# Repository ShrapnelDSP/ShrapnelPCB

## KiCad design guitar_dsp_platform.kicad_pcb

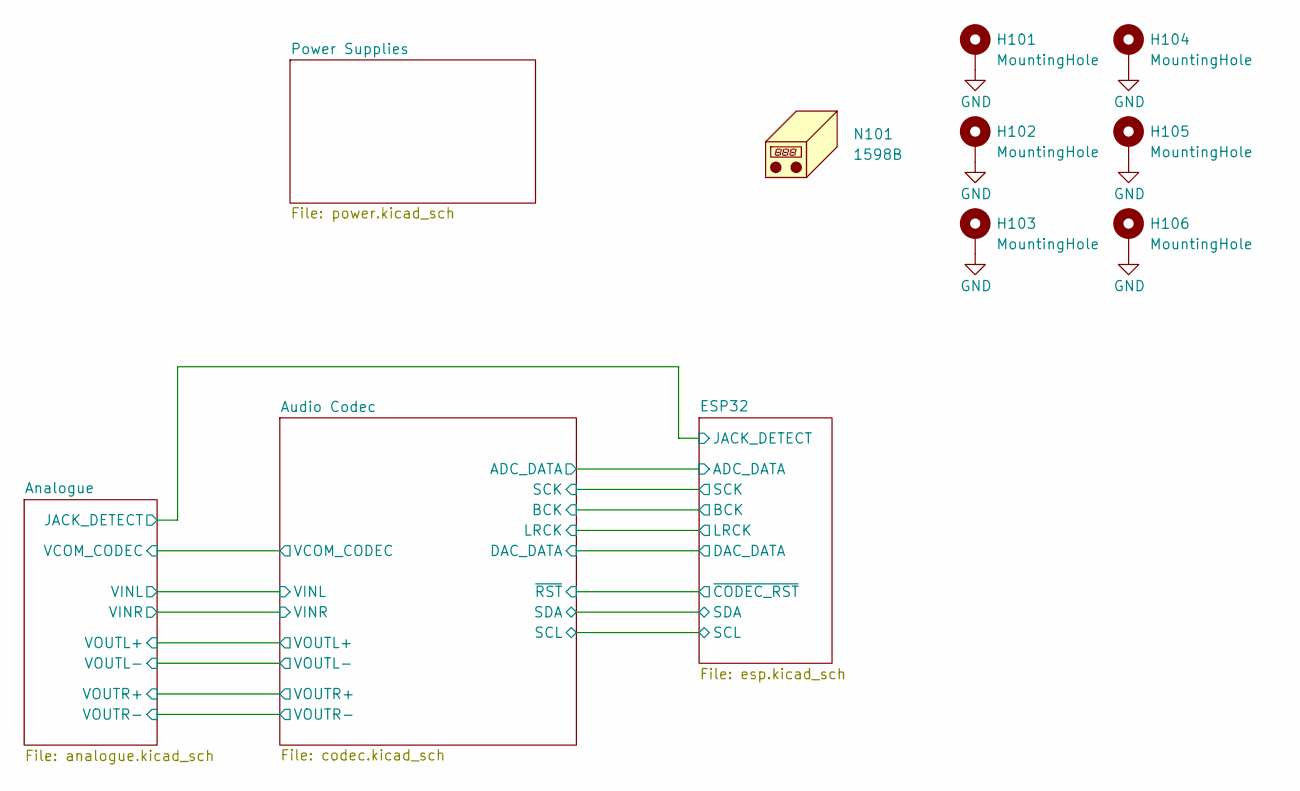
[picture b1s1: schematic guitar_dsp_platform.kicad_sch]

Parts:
H101, H102, H103, H104, H105, H106: MountingHole; 1598B_mounting_hole
N101: 1598B

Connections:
GND: H101.1, H102.1, H103.1, H104.1, H105.1, H106.1; also elsewhere on the board

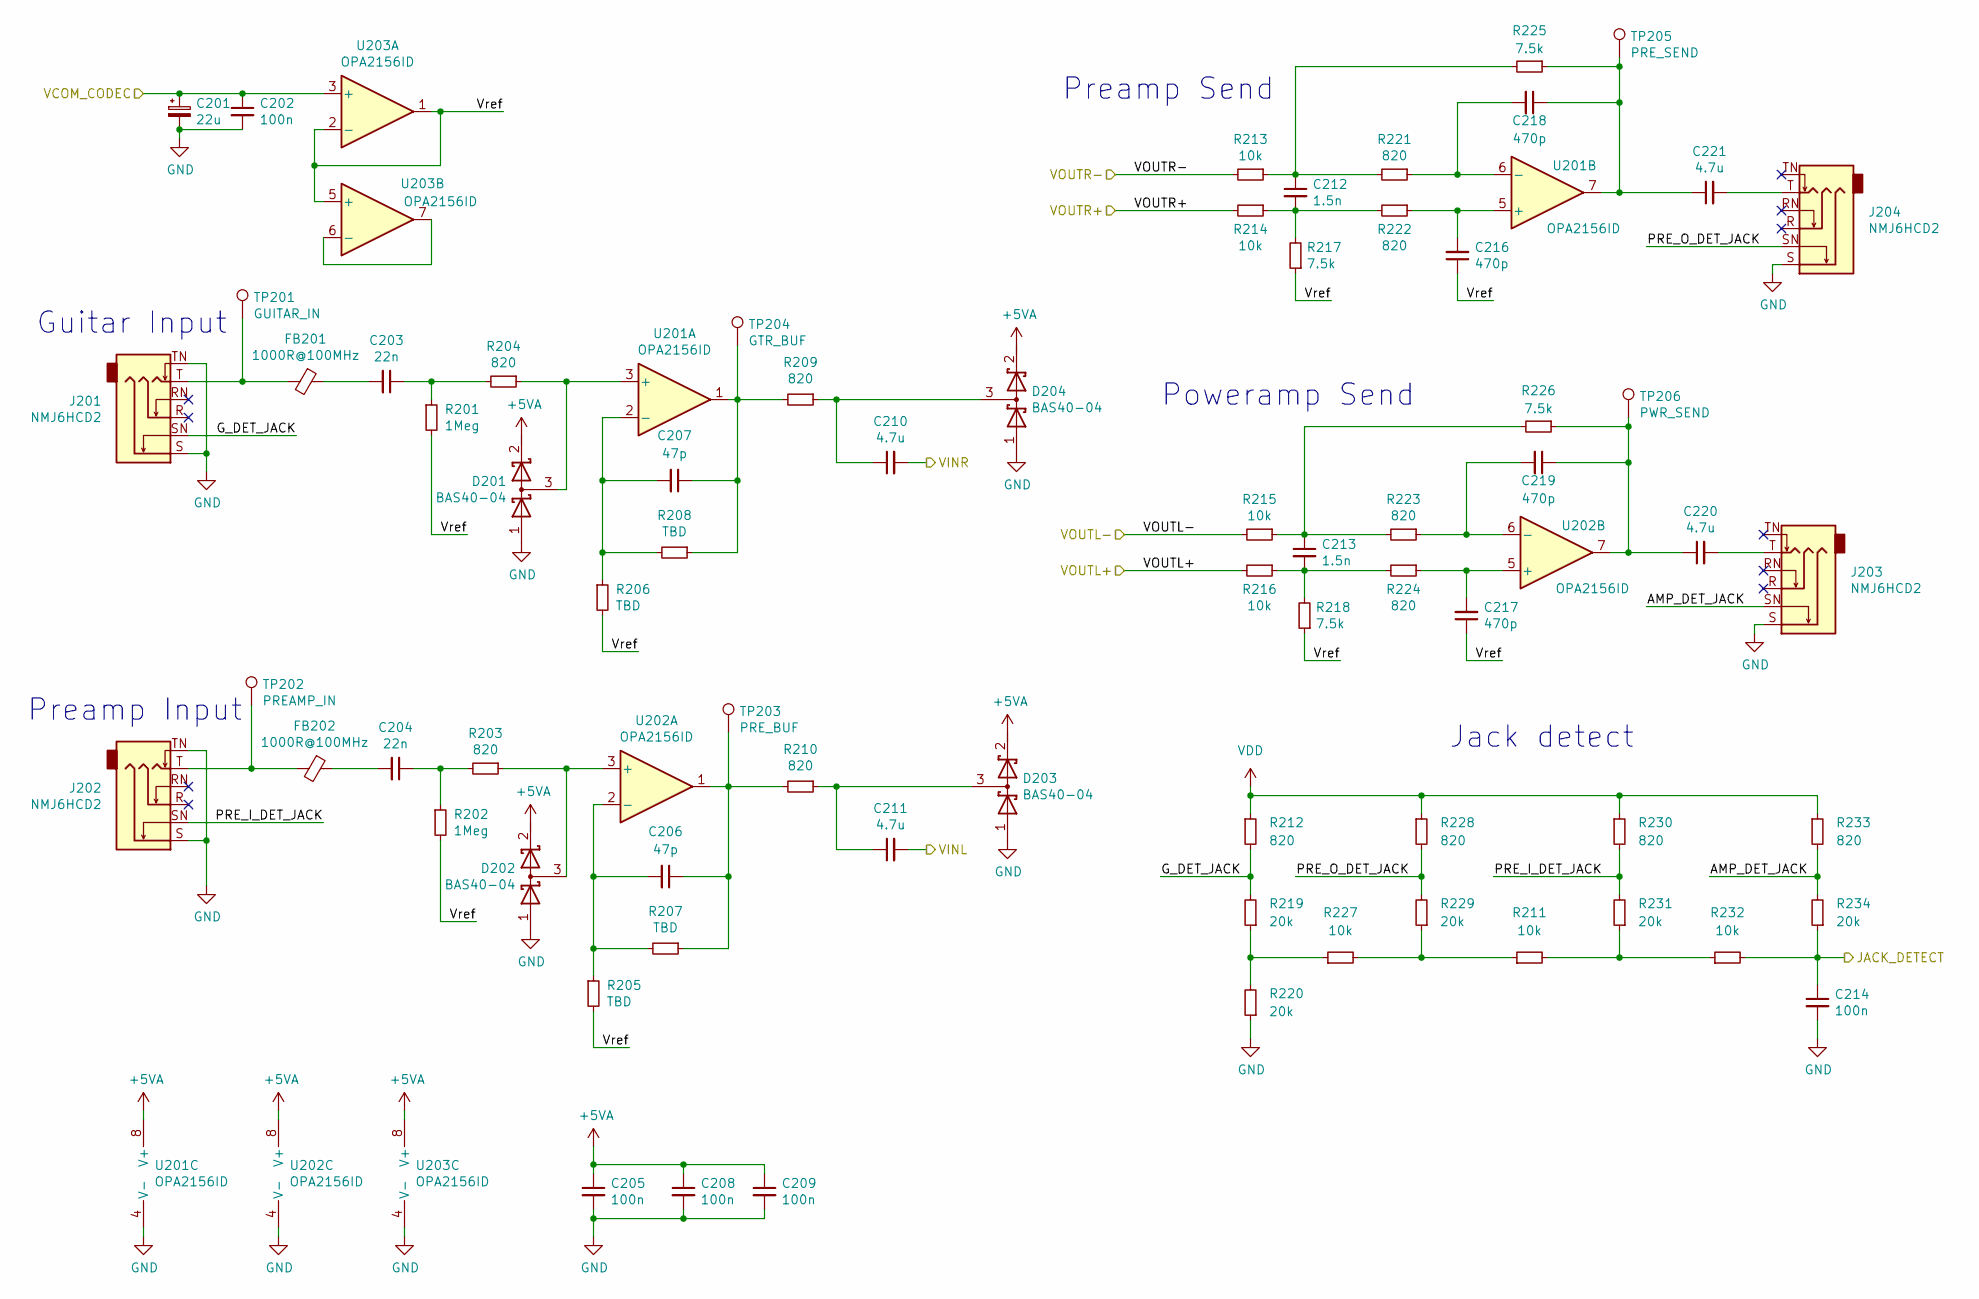
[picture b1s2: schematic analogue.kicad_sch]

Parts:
C201: 22u; CP_Elec_4x5.8
C202, C205, C208, C209, C214: 100n; C_0805_2012Metric_Pad1.18x1.45mm_HandSolder
C203, C204: 22n; C_0805_2012Metric_Pad1.18x1.45mm_HandSolder
C206, C207: 47p; C_0805_2012Metric_Pad1.18x1.45mm_HandSolder
C210, C211, C220, C221: 4.7u; C_Elec_4x5.8
C212, C213: 1.5n; C_0805_2012Metric_Pad1.18x1.45mm_HandSolder
C216, C217, C218, C219: 470p; C_0805_2012Metric_Pad1.18x1.45mm_HandSolder
D201, D202, D203, D204: BAS40-04; SOT-23
FB201, FB202: 1000R@100MHz; R_0805_2012Metric_Pad1.20x1.40mm_HandSolder
J201, J202, J203, J204: NMJ6HCD2; Jack_6.35mm_Neutrik_NMJ6HCD2_Horizontal
R201, R202: 1Meg; R_0805_2012Metric_Pad1.20x1.40mm_HandSolder
R203, R204, R209, R210, R212, R221, R222, R223, R224, R228, R230, R233: 820; R_0805_2012Metric_Pad1.20x1.40mm_HandSolder
R205, R206, R207, R208: TBD; R_0805_2012Metric_Pad1.20x1.40mm_HandSolder
R211, R213, R214, R215, R216, R227, R232: 10k; R_0805_2012Metric_Pad1.20x1.40mm_HandSolder
R217, R218, R225, R226: 7.5k; R_0805_2012Metric_Pad1.20x1.40mm_HandSolder
R219, R220, R229, R231, R234: 20k; R_0805_2012Metric_Pad1.20x1.40mm_HandSolder
TP201: GUITAR_IN; TestPoint_THTPad_D2.0mm_Drill1.0mm
TP202: PREAMP_IN; TestPoint_THTPad_D2.0mm_Drill1.0mm
TP203: PRE_BUF; TestPoint_THTPad_D2.0mm_Drill1.0mm
TP204: GTR_BUF; TestPoint_THTPad_D2.0mm_Drill1.0mm
TP205: PRE_SEND; TestPoint_THTPad_D2.0mm_Drill1.0mm
TP206: PWR_SEND; TestPoint_THTPad_D2.0mm_Drill1.0mm
U201, U202, U203: OPA2156ID; SOIC-8_3.9x4.9mm_P1.27mm

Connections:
+5VA: C205.1, C208.1, C209.1, D201.2 (K), D202.2 (K), D203.2 (K), D204.2 (K), U201.8 (V+), U202.8 (V+), U203.8 (V+); also elsewhere on the board
/Analogue/AMP_DET_JACK: J203.SN, R233.2, R234.2
/Analogue/G_DET_JACK: J201.SN, R212.2, R219.2
/Analogue/JACK_DETECT: C214.1, R232.2, R234.1; also elsewhere on the board
/Analogue/PRE_I_DET_JACK: J202.SN, R230.2, R231.2
/Analogue/PRE_O_DET_JACK: J204.SN, R228.2, R229.2
/Analogue/VCOM_CODEC: C201.1, C202.1, U203.3 (+); also elsewhere on the board
/Analogue/VINL: C211.2; also elsewhere on the board
/Analogue/VINR: C210.2; also elsewhere on the board
/Analogue/VOUTL+: R216.2; also elsewhere on the board
/Analogue/VOUTL-: R215.2; also elsewhere on the board
/Analogue/VOUTR+: R214.2; also elsewhere on the board
/Analogue/VOUTR-: R213.2; also elsewhere on the board
/Analogue/Vref: C216.1, C217.1, R201.2, R202.2, R205.2, R206.2, R217.1, R218.1, U203.1, U203.2 (-), U203.5 (+)
GND: C201.2, C202.2, C205.2, C208.2, C209.2, C214.2, D201.1 (A), D202.1 (A), D203.1 (A), D204.1 (A), J201.S, J201.TN, J202.S, J202.TN, J203.S, J204.S, R220.1, U201.4 (V-), U202.4 (V-), U203.4 (V-); also elsewhere on the board
unnamed: C203.1, R201.1, R204.2
unnamed: C203.2, FB201.1
unnamed: C204.1, R202.1, R203.2
unnamed: C204.2, FB202.1
unnamed: C206.1, R207.1, R210.2, TP203.1, U202.1
unnamed: C206.2, R205.1, R207.2, U202.2 (-)
unnamed: C207.1, R208.1, R209.2, TP204.1, U201.1
unnamed: C207.2, R206.1, R208.2, U201.2 (-)
unnamed: C210.1, D204.3 (common), R209.1
unnamed: C211.1, D203.3 (common), R210.1
unnamed: C212.1, R213.1, R221.2, R225.2
unnamed: C212.2, R214.1, R217.2, R222.2
unnamed: C213.1, R215.1, R223.2, R226.2
unnamed: C213.2, R216.1, R218.2, R224.2
unnamed: C216.2, R222.1, U201.5 (+)
unnamed: C217.2, R224.1, U202.5 (+)
unnamed: C218.1, C221.1, R225.1, TP205.1, U201.7
unnamed: C218.2, R221.1, U201.6 (-)
unnamed: C219.1, C220.1, R226.1, TP206.1, U202.7
unnamed: C219.2, R223.1, U202.6 (-)
unnamed: C220.2, J203.T
unnamed: C221.2, J204.T
unnamed: D201.3 (common), R204.1, U201.3 (+)
unnamed: D202.3 (common), R203.1, U202.3 (+)
unnamed: FB201.2, J201.T, TP201.1
unnamed: FB202.2, J202.T, TP202.1
unnamed: R211.1, R227.2, R229.1
unnamed: R211.2, R231.1, R232.1
unnamed: R219.1, R220.2, R227.1
unnamed: U203.6 (-), U203.7
VDD: R212.1, R228.1, R230.1, R233.1; also elsewhere on the board

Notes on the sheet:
Preamp Input
Guitar Input
Preamp Send
Poweramp Send
Jack detect

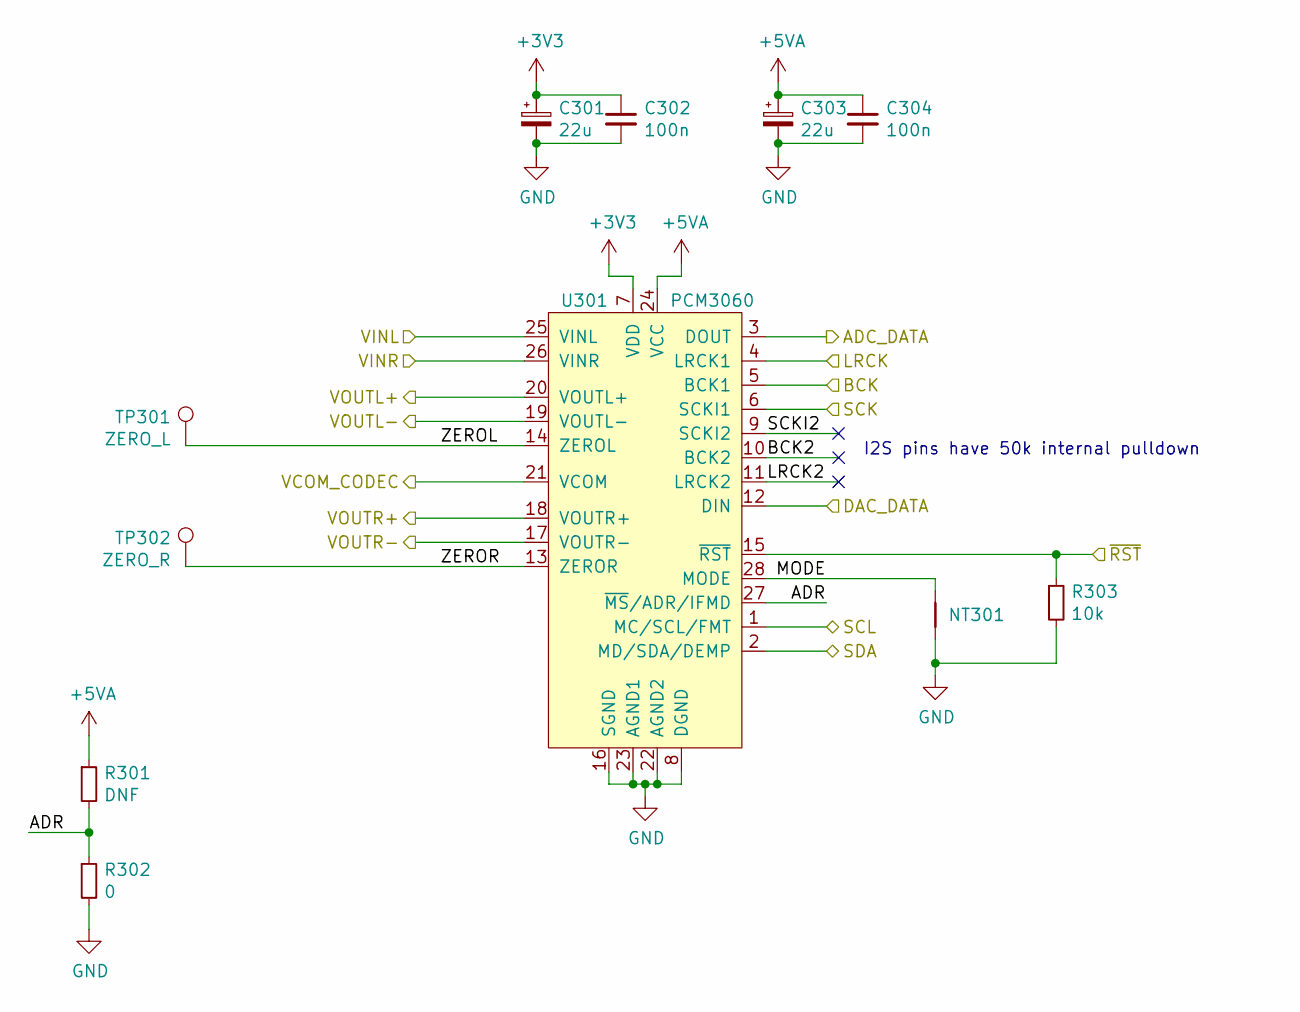
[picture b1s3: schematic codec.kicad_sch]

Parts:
C301, C303: 22u; CP_Elec_4x5.8
C302, C304: 100n; C_0805_2012Metric_Pad1.18x1.45mm_HandSolder
NT301: Net-Tie_2; NetTie-2_SMD_Pad0.5mm
R301: DNF; R_0805_2012Metric_Pad1.20x1.40mm_HandSolder
R302: 0; R_0805_2012Metric_Pad1.20x1.40mm_HandSolder
R303: 10k; R_0805_2012Metric_Pad1.20x1.40mm_HandSolder
TP301: ZERO_L; TestPoint_Pad_1.0x1.0mm
TP302: ZERO_R; TestPoint_Pad_1.0x1.0mm
U301: PCM3060; TSSOP-28_4.4x9.7mm_P0.65mm

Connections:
+3V3: C301.1, C302.1, U301.7 (VDD); also elsewhere on the board
+5VA: C303.1, C304.1, R301.1, U301.24 (VCC); also elsewhere on the board
/Analogue/VCOM_CODEC: U301.21 (VCOM); also elsewhere on the board
/Analogue/VINL: U301.25 (VINL); also elsewhere on the board
/Analogue/VINR: U301.26 (VINR); also elsewhere on the board
/Analogue/VOUTL+: U301.20 (VOUTL+); also elsewhere on the board
/Analogue/VOUTL-: U301.19 (VOUTL-); also elsewhere on the board
/Analogue/VOUTR+: U301.18 (VOUTR+); also elsewhere on the board
/Analogue/VOUTR-: U301.17 (VOUTR-); also elsewhere on the board
/Audio Codec/ADC_DATA: U301.3 (DOUT); also elsewhere on the board
/Audio Codec/ADR: R301.2, R302.1, U301.27 (~MS/ADR/IFMD)
/Audio Codec/BCK2: U301.10 (BCK2)
/Audio Codec/LRCK2: U301.11 (LRCK2)
/Audio Codec/MODE: NT301.2, U301.28 (MODE)
/Audio Codec/SCKI2: U301.9 (SCKI2)
/Audio Codec/ZEROL: TP301.1, U301.14 (ZEROL)
/Audio Codec/ZEROR: TP302.1, U301.13 (ZEROR)
/Audio Codec/~RST: R303.1, U301.15 (~RST); also elsewhere on the board
/ESP32/BCK: U301.5 (BCK1); also elsewhere on the board
/ESP32/DAC_DATA: U301.12 (DIN); also elsewhere on the board
/ESP32/LRCK: U301.4 (LRCK1); also elsewhere on the board
/ESP32/SCK: U301.6 (SCKI1); also elsewhere on the board
/ESP32/SCL: U301.1 (MC/SCL/FMT); also elsewhere on the board
/ESP32/SDA: U301.2 (MD/SDA/DEMP); also elsewhere on the board
GND: C301.2, C302.2, C303.2, C304.2, NT301.1, R302.2, R303.2, U301.8 (DGND), U301.16 (SGND), U301.22 (AGND2), U301.23 (AGND1); also elsewhere on the board

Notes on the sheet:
I2S pins have 50k internal pulldown

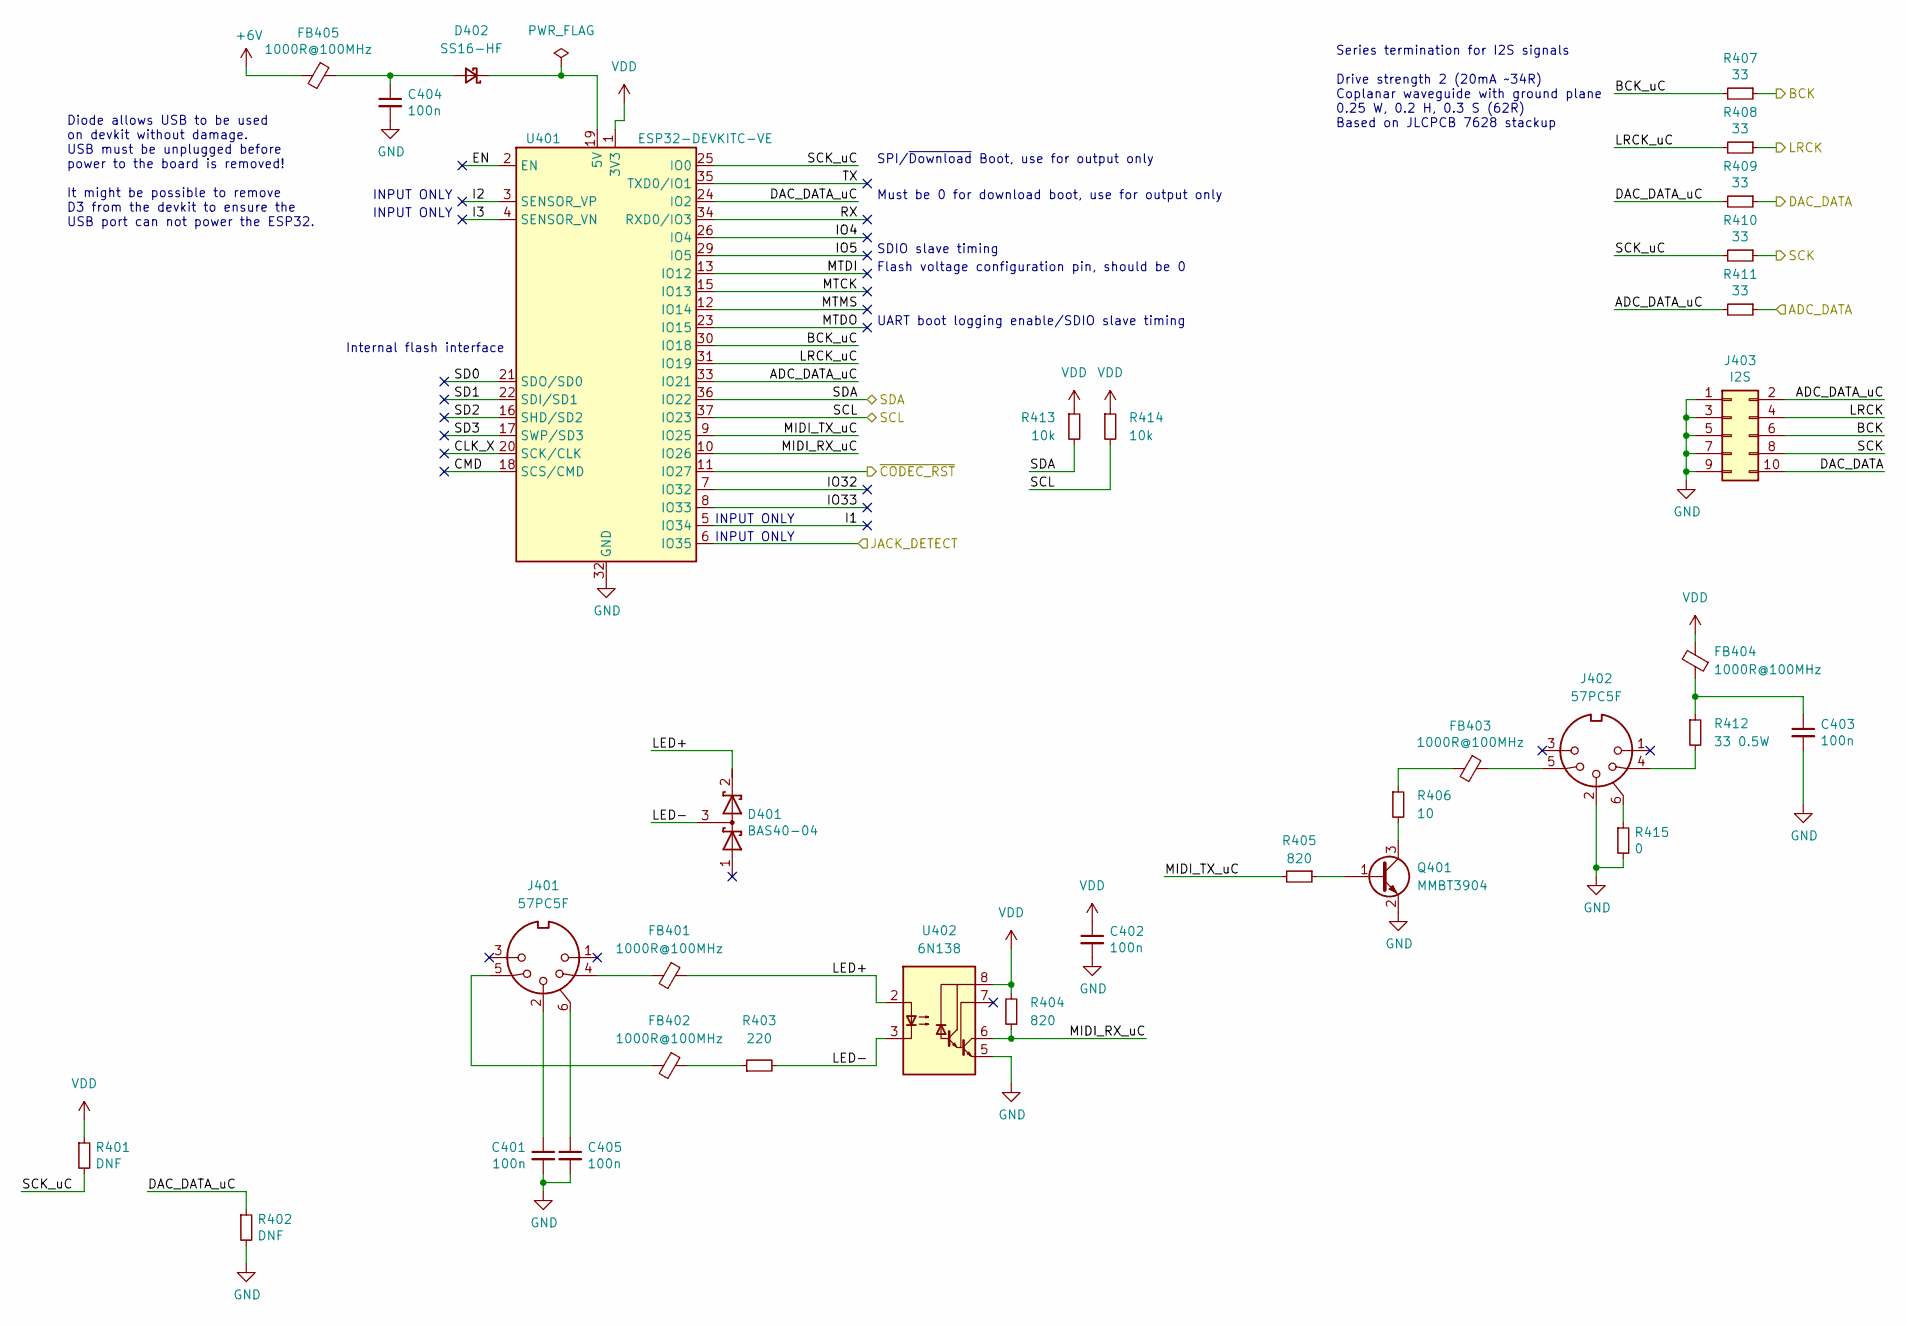
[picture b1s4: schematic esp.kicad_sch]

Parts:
C401, C402, C403, C404, C405: 100n; C_0805_2012Metric_Pad1.18x1.45mm_HandSolder
D401: BAS40-04; SOT-23
D402: SS16-HF; D_SMA_Handsoldering
FB401, FB402, FB403, FB404, FB405: 1000R@100MHz; R_0805_2012Metric_Pad1.20x1.40mm_HandSolder
J401, J402: 57PC5F
J403: I2S; PinHeader_2x05_P2.54mm_Vertical
Q401: MMBT3904; SOT-23
R401, R402: DNF; R_0805_2012Metric_Pad1.20x1.40mm_HandSolder
R403: 220; R_0805_2012Metric_Pad1.20x1.40mm_HandSolder
R404, R405: 820; R_0805_2012Metric_Pad1.20x1.40mm_HandSolder
R406: 10; R_0805_2012Metric_Pad1.20x1.40mm_HandSolder
R407, R408, R409, R410, R411: 33; R_0805_2012Metric_Pad1.20x1.40mm_HandSolder
R412: 33 0.5W; R_1206_3216Metric_Pad1.30x1.75mm_HandSolder
R413, R414: 10k; R_0805_2012Metric_Pad1.20x1.40mm_HandSolder
R415: 0; R_0805_2012Metric_Pad1.20x1.40mm_HandSolder
U401: ESP32-DEVKITC-VE; ESP32_DevkitC
U402: 6N138; DIP-8_W8.89mm_SMDSocket_LongPads

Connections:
+6V: FB405.2; also elsewhere on the board
/Analogue/JACK_DETECT: U401.6 (IO35); also elsewhere on the board
/Audio Codec/ADC_DATA: R411.1; also elsewhere on the board
/Audio Codec/~RST: U401.11 (IO27); also elsewhere on the board
/ESP32/ADC_DATA_uC: J403.2, R411.2, U401.33 (IO21)
/ESP32/BCK: J403.6, R407.1; also elsewhere on the board
/ESP32/BCK_uC: R407.2, U401.30 (IO18)
/ESP32/CLK_X: U401.20 (SCK/CLK)
/ESP32/CMD: U401.18 (SCS/CMD)
/ESP32/DAC_DATA: J403.10, R409.1; also elsewhere on the board
/ESP32/DAC_DATA_uC: R402.1, R409.2, U401.24 (IO2)
/ESP32/EN: U401.2 (EN)
/ESP32/I1: U401.5 (IO34)
/ESP32/I2: U401.3 (SENSOR_VP)
/ESP32/I3: U401.4 (SENSOR_VN)
/ESP32/IO4: U401.26 (IO4)
/ESP32/IO5: U401.29 (IO5)
/ESP32/IO32: U401.7 (IO32)
/ESP32/IO33: U401.8 (IO33)
/ESP32/LED+: D401.2 (K), FB401.1, U402.2 (C1)
/ESP32/LED-: D401.3 (common), R403.2, U402.3 (C2)
/ESP32/LRCK: J403.4, R408.1; also elsewhere on the board
/ESP32/LRCK_uC: R408.2, U401.31 (IO19)
/ESP32/MIDI_RX_uC: R404.1, U401.10 (IO26), U402.6 (VO2)
/ESP32/MIDI_TX_uC: R405.2, U401.9 (IO25)
/ESP32/MTCK: U401.15 (IO13)
/ESP32/MTDI: U401.13 (IO12)
/ESP32/MTDO: U401.23 (IO15)
/ESP32/MTMS: U401.12 (IO14)
/ESP32/RX: U401.34 (RXD0/IO3)
/ESP32/SCK: J403.8, R410.1; also elsewhere on the board
/ESP32/SCK_uC: R401.2, R410.2, U401.25 (IO0)
/ESP32/SCL: R414.2, U401.37 (IO23); also elsewhere on the board
/ESP32/SD0: U401.21 (SDO/SD0)
/ESP32/SD1: U401.22 (SDI/SD1)
/ESP32/SD2: U401.16 (SHD/SD2)
/ESP32/SD3: U401.17 (SWP/SD3)
/ESP32/SDA: R413.2, U401.36 (IO22); also elsewhere on the board
/ESP32/TX: U401.35 (TXD0/IO1)
GND: C401.2, C402.2, C403.2, C404.2, C405.2, J402.2, J403.1, J403.3, J403.5, J403.7, J403.9, Q401.2 (E), R402.2, R415.2, U401.14 (GND), U401.32 (GND), U401.38 (GND), U402.5 (GND); also elsewhere on the board
unnamed: C401.1, J401.2
unnamed: C403.1, FB404.1, R412.1
unnamed: C404.1, D402.2 (A), FB405.1
unnamed: C405.1, J401.6, J401.7
unnamed: D402.1 (K), U401.19 (5V)
unnamed: FB401.2, J401.4
unnamed: FB402.1, R403.1
unnamed: FB402.2, J401.5
unnamed: FB403.1, J402.5
unnamed: FB403.2, R406.1
unnamed: J402.4, R412.2
unnamed: J402.6, J402.7, R415.1
unnamed: Q401.1 (B), R405.1
unnamed: Q401.3 (C), R406.2
VDD: C402.1, FB404.2, R401.1, R404.2, R413.1, R414.1, U401.1 (3V3), U402.8 (VCC); also elsewhere on the board

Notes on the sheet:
Diode allows USB to be used on devkit without damage. USB must be unplugged before power to the board is removed! It might be possible to remove D3 from the devkit to ensure the USB port can not power the ESP32.
Internal flash interface
INPUT ONLY
SPI/~{Download} Boot, use for output only
Must be 0 for download boot, use for output only
SDIO slave timing
Flash voltage configuration pin, should be 0
UART boot logging enable/SDIO slave timing
Series termination for I2S signals Drive strength 2 (20mA ~34R) Coplanar waveguide with ground plane 0.25 W, 0.2 H, 0.3 S (62R) Based on JLCPCB 7628 stackup

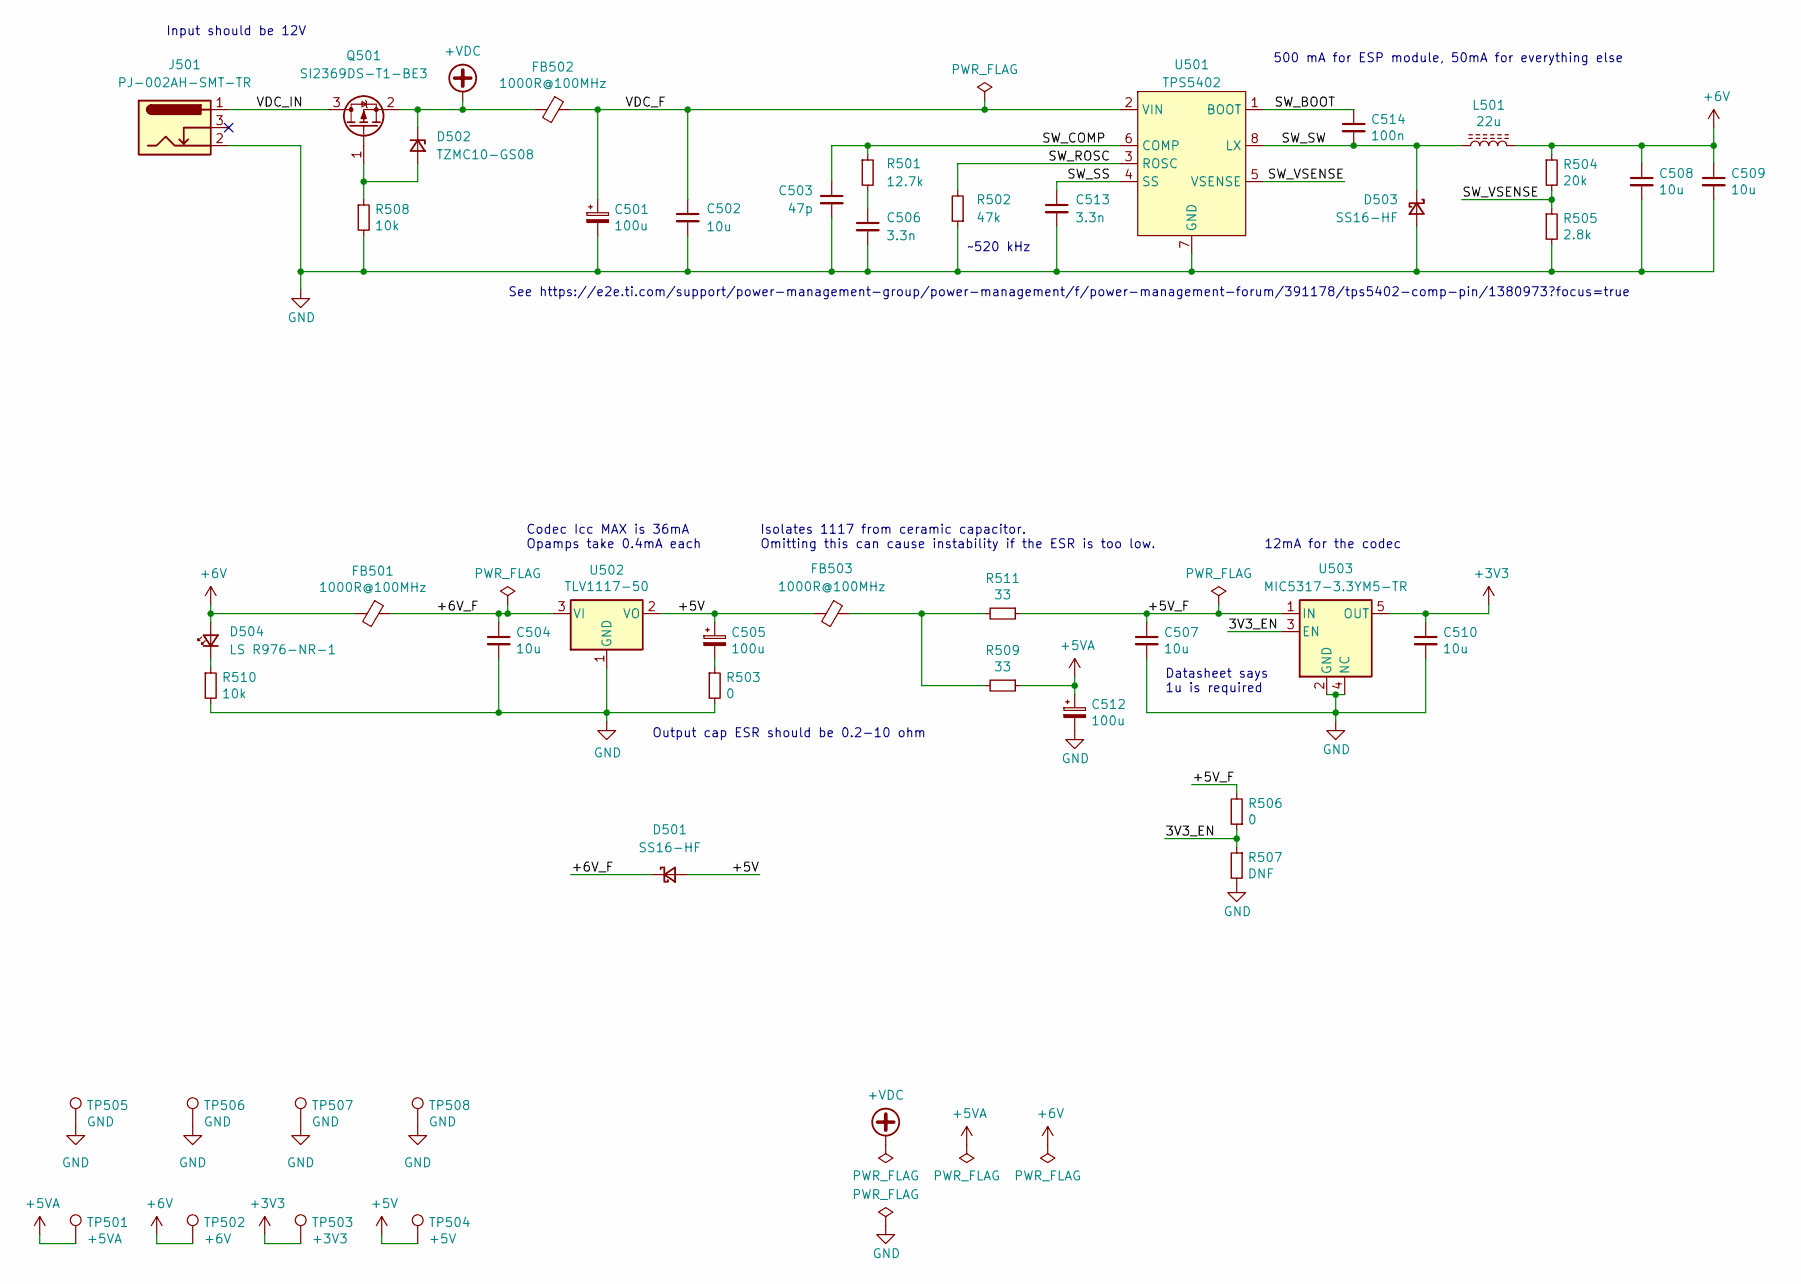
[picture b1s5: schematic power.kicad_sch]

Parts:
C501, C505, C512: 100u; CP_Elec_6.3x7.7
C502, C504, C507, C508, C509, C510: 10u; C_0805_2012Metric_Pad1.18x1.45mm_HandSolder
C503: 47p; C_0805_2012Metric_Pad1.18x1.45mm_HandSolder
C506, C513: 3.3n; C_0805_2012Metric_Pad1.18x1.45mm_HandSolder
C514: 100n; C_0805_2012Metric_Pad1.18x1.45mm_HandSolder
D501, D503: SS16-HF; D_SMA_Handsoldering
D502: TZMC10-GS08; D_MiniMELF
D504: LS R976-NR-1; LED_0805_2012Metric_Castellated
FB501, FB502, FB503: 1000R@100MHz; R_0805_2012Metric_Pad1.20x1.40mm_HandSolder
J501: PJ-002AH-SMT-TR; CUI_PJ-002AH-SMT-TR
L501: 22u; L_Taiyo-Yuden_NR-50xx_HandSoldering
Q501: SI2369DS-T1-BE3; SOT-23
R501: 12.7k; R_0805_2012Metric_Pad1.20x1.40mm_HandSolder
R502: 47k; R_0805_2012Metric_Pad1.20x1.40mm_HandSolder
R503, R506: 0; R_0805_2012Metric_Pad1.20x1.40mm_HandSolder
R504: 20k; R_0805_2012Metric_Pad1.20x1.40mm_HandSolder
R505: 2.8k; R_0805_2012Metric_Pad1.20x1.40mm_HandSolder
R507: DNF; R_0805_2012Metric_Pad1.20x1.40mm_HandSolder
R508, R510: 10k; R_0805_2012Metric_Pad1.20x1.40mm_HandSolder
R509, R511: 33; R_0805_2012Metric_Pad1.20x1.40mm_HandSolder
TP501: +5VA; TestPoint_THTPad_D2.0mm_Drill1.0mm
TP502: +6V; TestPoint_THTPad_D2.0mm_Drill1.0mm
TP503: +3V3; TestPoint_THTPad_D2.0mm_Drill1.0mm
TP504: +5V; TestPoint_THTPad_D2.0mm_Drill1.0mm
TP505, TP506, TP507, TP508: GND; TestPoint_THTPad_D2.0mm_Drill1.0mm
U501: TPS5402; SOIC-8_3.9x4.9mm_P1.27mm
U502: TLV1117-50; SOT-223-3_TabPin2
U503: MIC5317-3.3YM5-TR; SOT-23-5_HandSoldering

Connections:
+3V3: C510.1, TP503.1, U503.5 (OUT); also elsewhere on the board
+5V: C505.1, D501.2 (A), FB503.2, TP504.1, U502.2 (VO)
+5VA: C512.1, R509.1, TP501.1; also elsewhere on the board
+6V: C508.1, C509.1, D504.2 (A), FB501.2, L501.2, R504.1, TP502.1; also elsewhere on the board
+VDC: D502.1 (K), FB502.2, Q501.2 (S)
/Power Supplies/3V3_EN: R506.1, R507.1, U503.3 (EN)
/Power Supplies/+5V_F: C507.1, R506.2, R511.1, U503.1 (IN)
/Power Supplies/+6V_F: C504.1, D501.1 (K), FB501.1, U502.3 (VI)
/Power Supplies/SW_BOOT: C514.1, U501.1 (BOOT)
/Power Supplies/SW_COMP: C503.1, R501.1, U501.6 (COMP)
/Power Supplies/SW_ROSC: R502.2, U501.3 (ROSC)
/Power Supplies/SW_SS: C513.1, U501.4 (SS)
/Power Supplies/SW_SW: C514.2, D503.1 (K), L501.1, U501.8 (LX)
/Power Supplies/SW_VSENSE: R504.2, R505.1, U501.5 (VSENSE)
/Power Supplies/VDC_F: C501.1, C502.1, FB502.1, U501.2 (VIN)
/Power Supplies/VDC_IN: J501.1, Q501.3 (D)
GND: C501.2, C502.2, C503.2, C504.2, C506.2, C507.2, C508.2, C509.2, C510.2, C512.2, C513.2, D503.2 (A), J501.2, R502.1, R503.2, R505.2, R507.2, R508.2, R510.2, TP505.1, TP506.1, TP507.1, TP508.1, U501.7 (GND), U502.1 (GND), U503.2 (GND), U503.4 (NC); also elsewhere on the board
unnamed: C505.2, R503.1
unnamed: C506.1, R501.2
unnamed: D502.2 (A), Q501.1 (G), R508.1
unnamed: D504.1 (K), R510.1
unnamed: FB503.1, R509.2, R511.2

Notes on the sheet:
Input should be 12V
See https://e2e.ti.com/support/power-management-group/power-management/f/power-management-forum/391178/tps5402-comp-pin/1380973?focus=true
Codec Icc MAX is 36mA Opamps take 0.4mA each
Output cap ESR should be 0.2-10 ohm
Isolates 1117 from ceramic capacitor. Omitting this can cause instability if the ESR is too low.
~520 kHz
Datasheet says 1u is required
12mA for the codec
500 mA for ESP module, 50mA for everything else

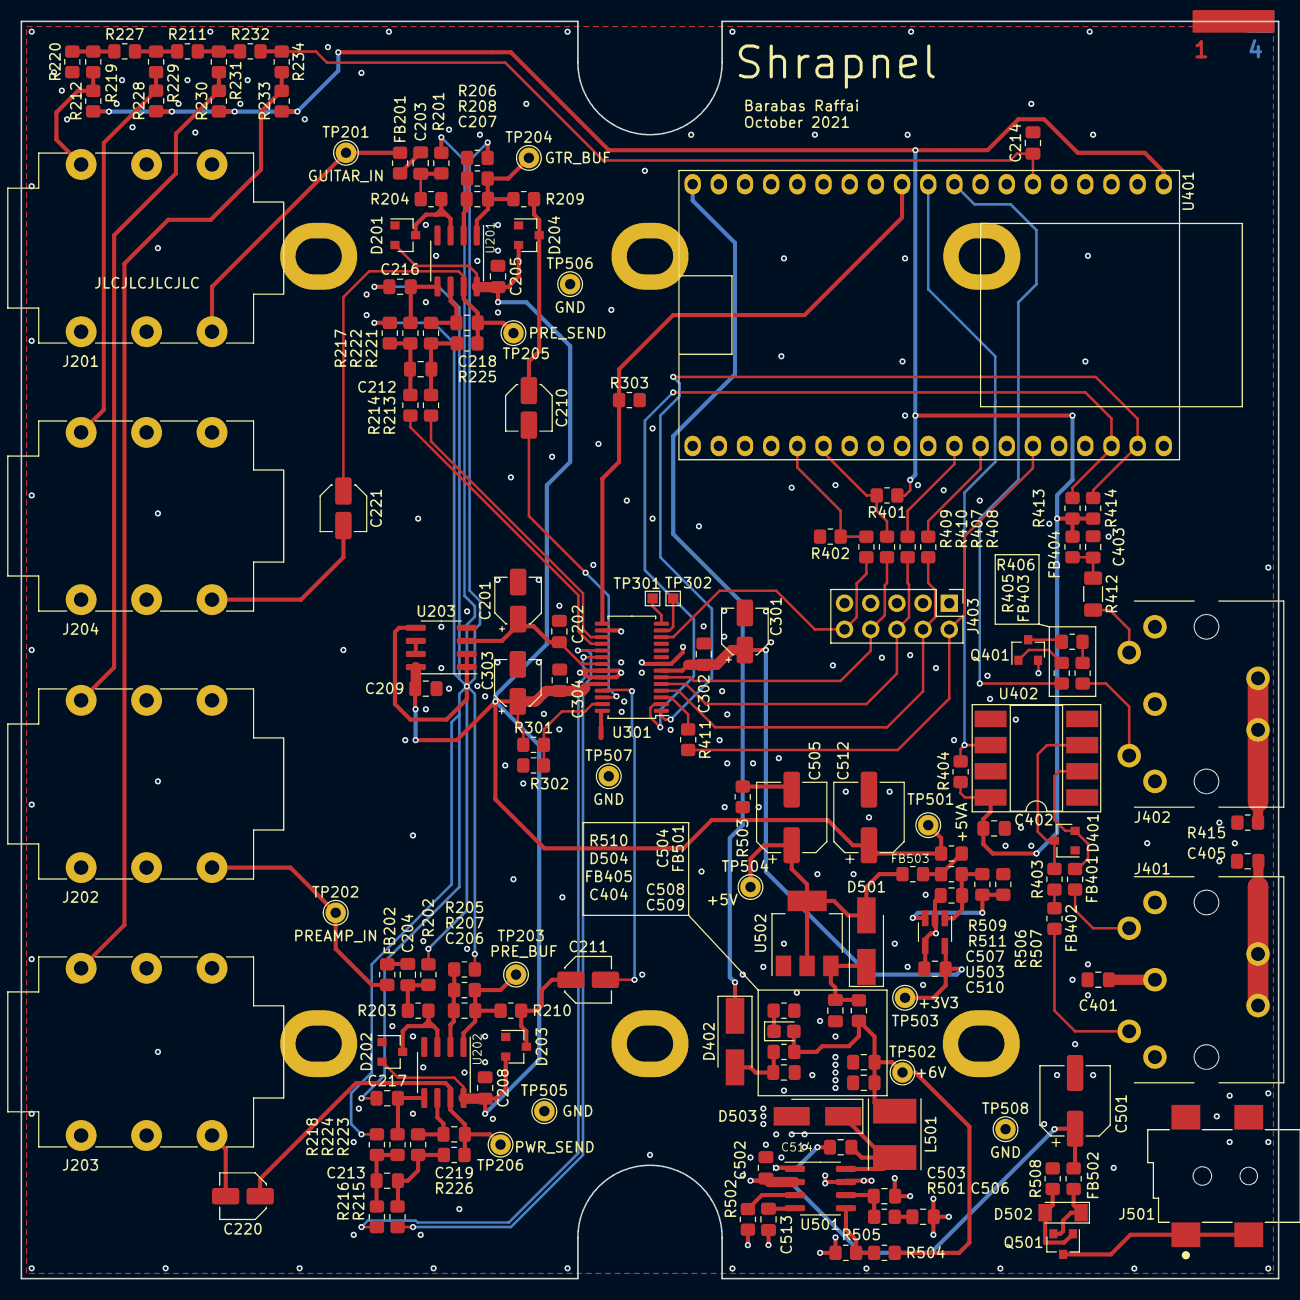
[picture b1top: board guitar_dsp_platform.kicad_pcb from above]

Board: 4 copper layers, 122.0 x 122.0 mm, 168 parts (0 on the bottom side), 101 nets.

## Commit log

2021-08-31 Add MIDI, convert to nightly kicad
2021-09-05 Working on schematic
2021-09-06 Review PSU, add footprints for all components
2021-09-07 Tweak layout
2021-09-11 Schematic reviewed, assign PN to all parts
2021-09-11 Start BOM tidy up
2021-09-12 Update 3D models to work with FreeCAD StepUp plugin
2021-09-12 Update some part numbers for in-stock parts
2021-09-18 WIP substitute parts
2021-09-18 Add new switchmode power supply
2021-09-19 Complete power supply design
2021-09-20 Ready for layout
2021-09-20 Layout first draft
2021-09-25 Mechanical tweaks of I/O
2021-09-28 Clean up layout, add testpoints, layer markers
2021-09-29 Minor layout tweaks
2021-10-14 Final BOM changes
2021-10-17 Tweak mechanical design
    1/4 inch jacks are now flush with the faceplate. Reduced the gap between
    MIDI jack and back faceplate.
2021-10-19 Space jacks in increments of 1.2 mm (spacer thickness)
    Delete non-mechanical through holes. This board can be 3D printed to
    check mechanical fit with enclosure.
2021-10-22 Adjust jack position after mechanical checks
    Jacks will require two internal 1.2mm washers, and the external washer
    supplied with the jacks.
2021-10-26 Resolve some issues
    - Add missing MIDI connector pins to symbol
    - Isolate low-ESR capacitors from 1117
    - Fix DRC errors in footprints
2021-10-26 Add silkscreen lines for mounting screw keep-out
2021-10-28 Exports setup for JLCPCB
2021-10-28 Replace mounting holes with plated slots
2021-11-09 Fix incorrect part number
2021-11-23 Update to kicad 6 rc 1
2021-11-23 resave schematic
